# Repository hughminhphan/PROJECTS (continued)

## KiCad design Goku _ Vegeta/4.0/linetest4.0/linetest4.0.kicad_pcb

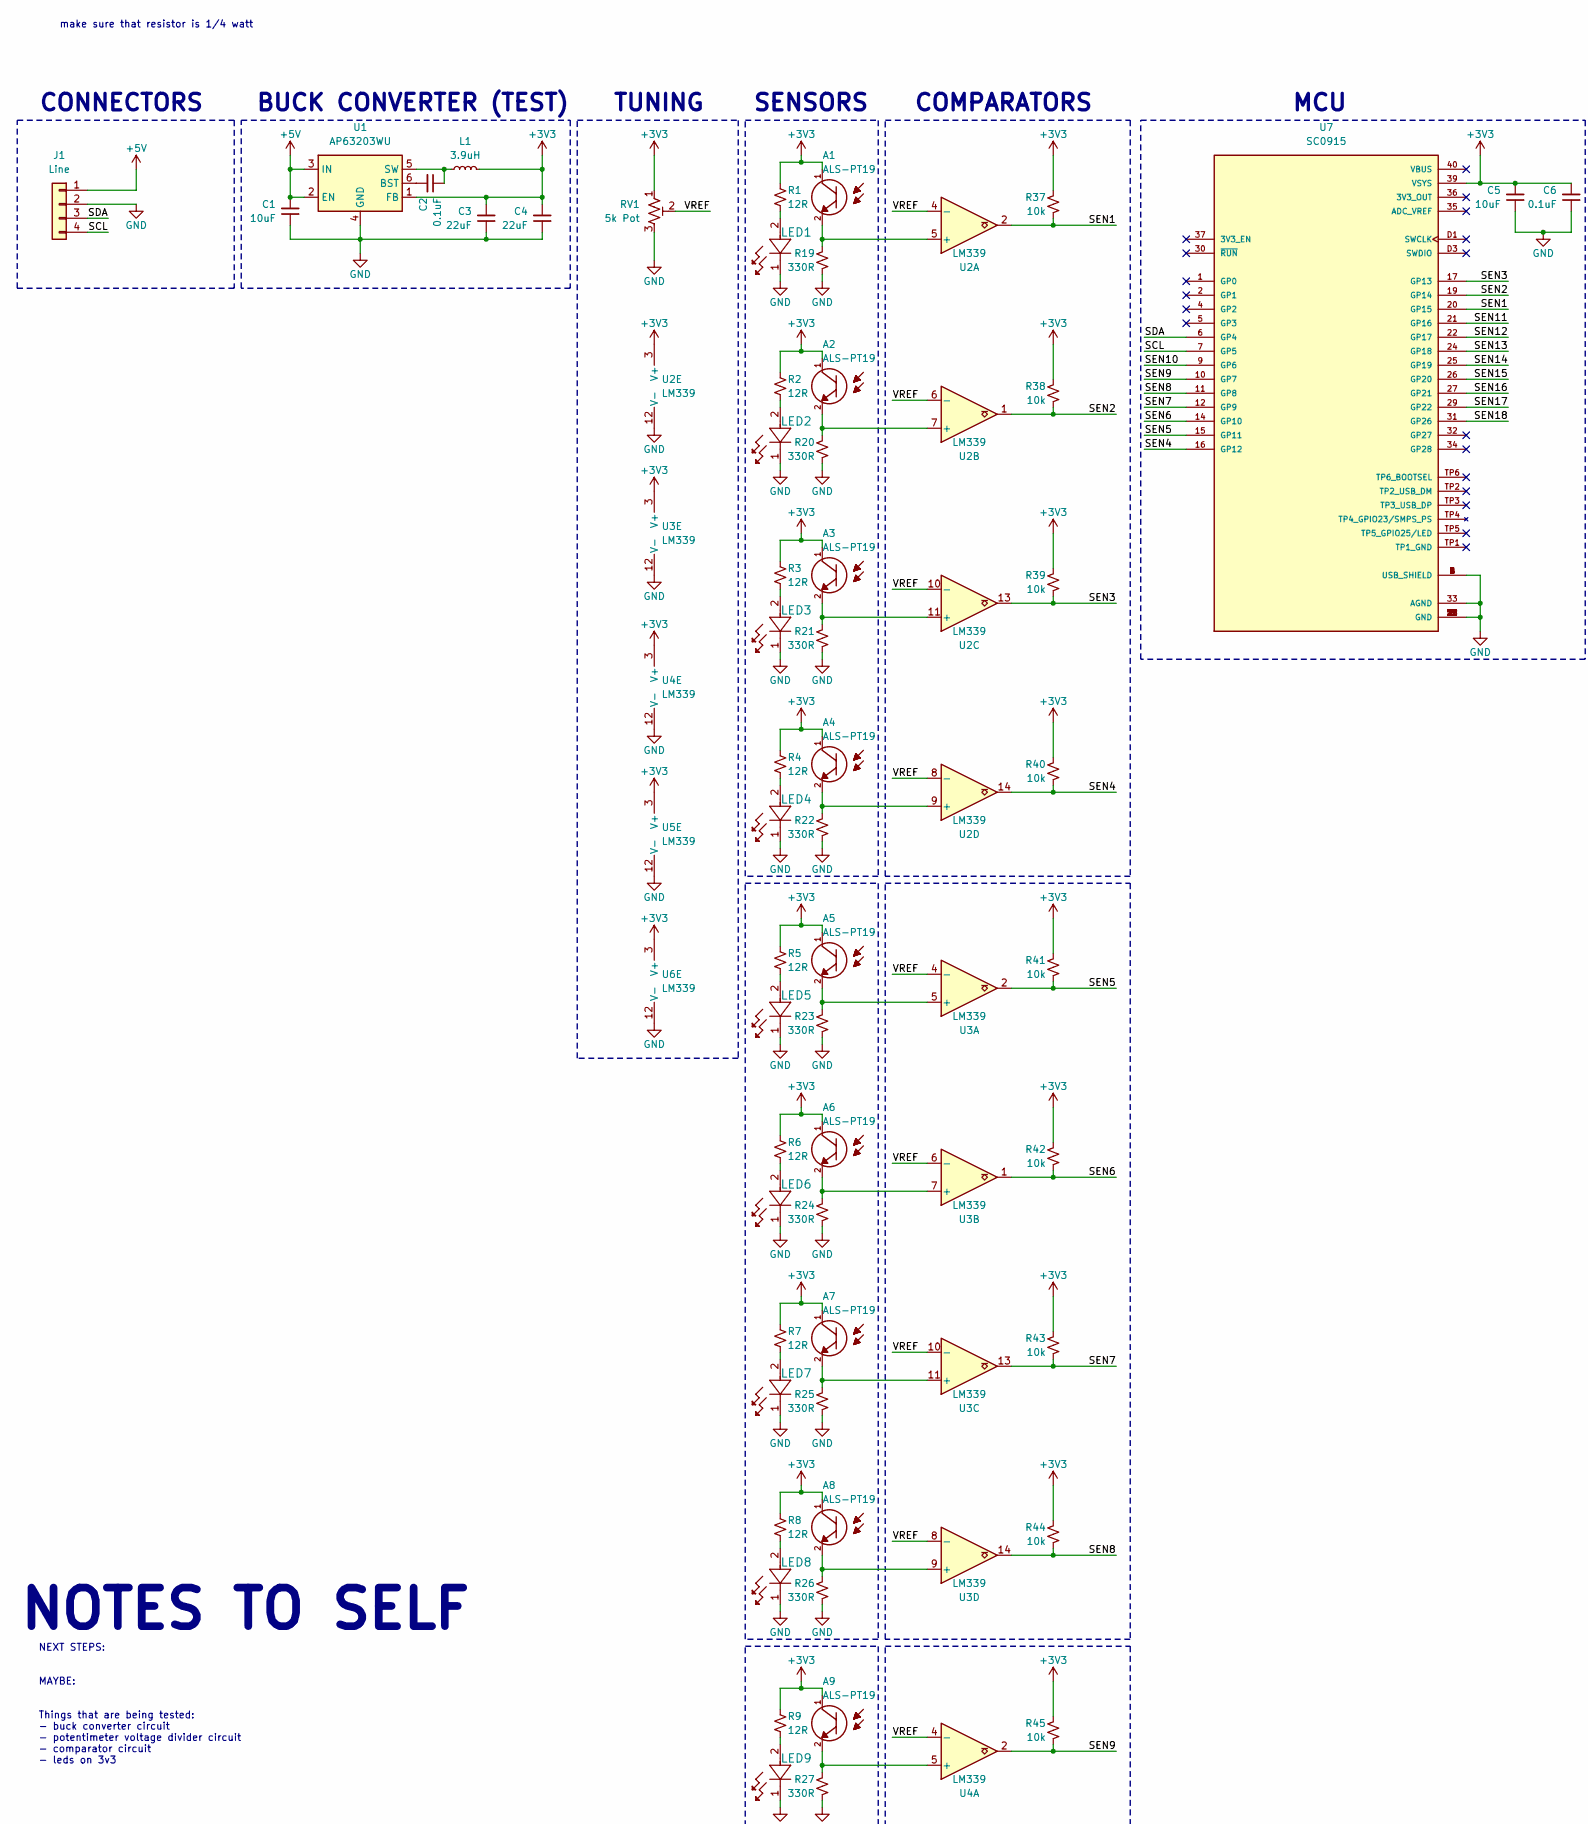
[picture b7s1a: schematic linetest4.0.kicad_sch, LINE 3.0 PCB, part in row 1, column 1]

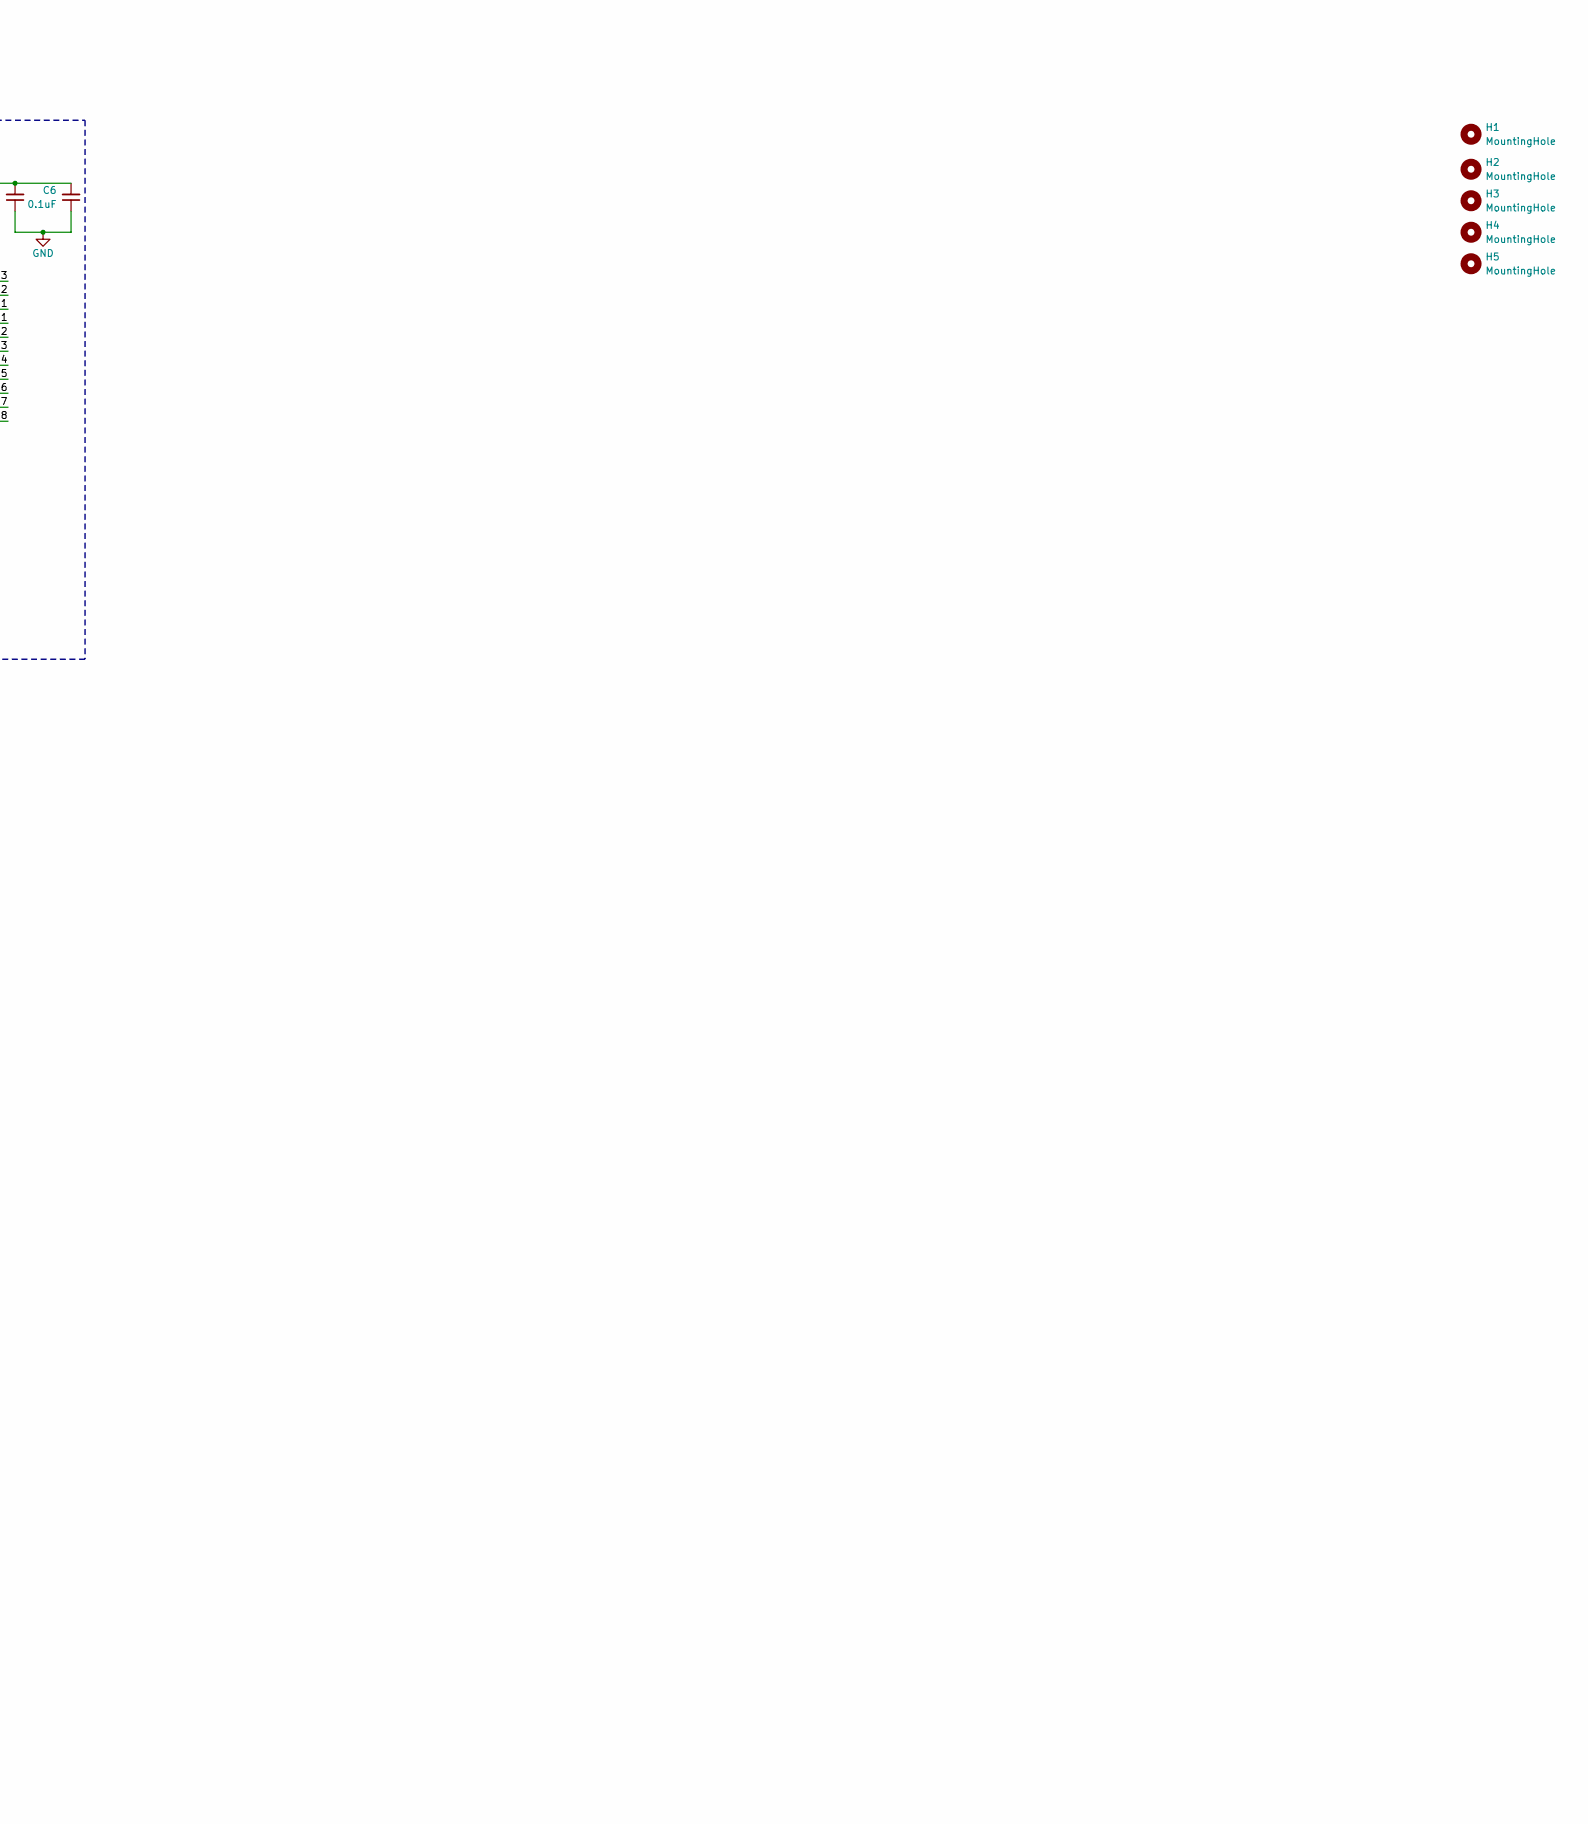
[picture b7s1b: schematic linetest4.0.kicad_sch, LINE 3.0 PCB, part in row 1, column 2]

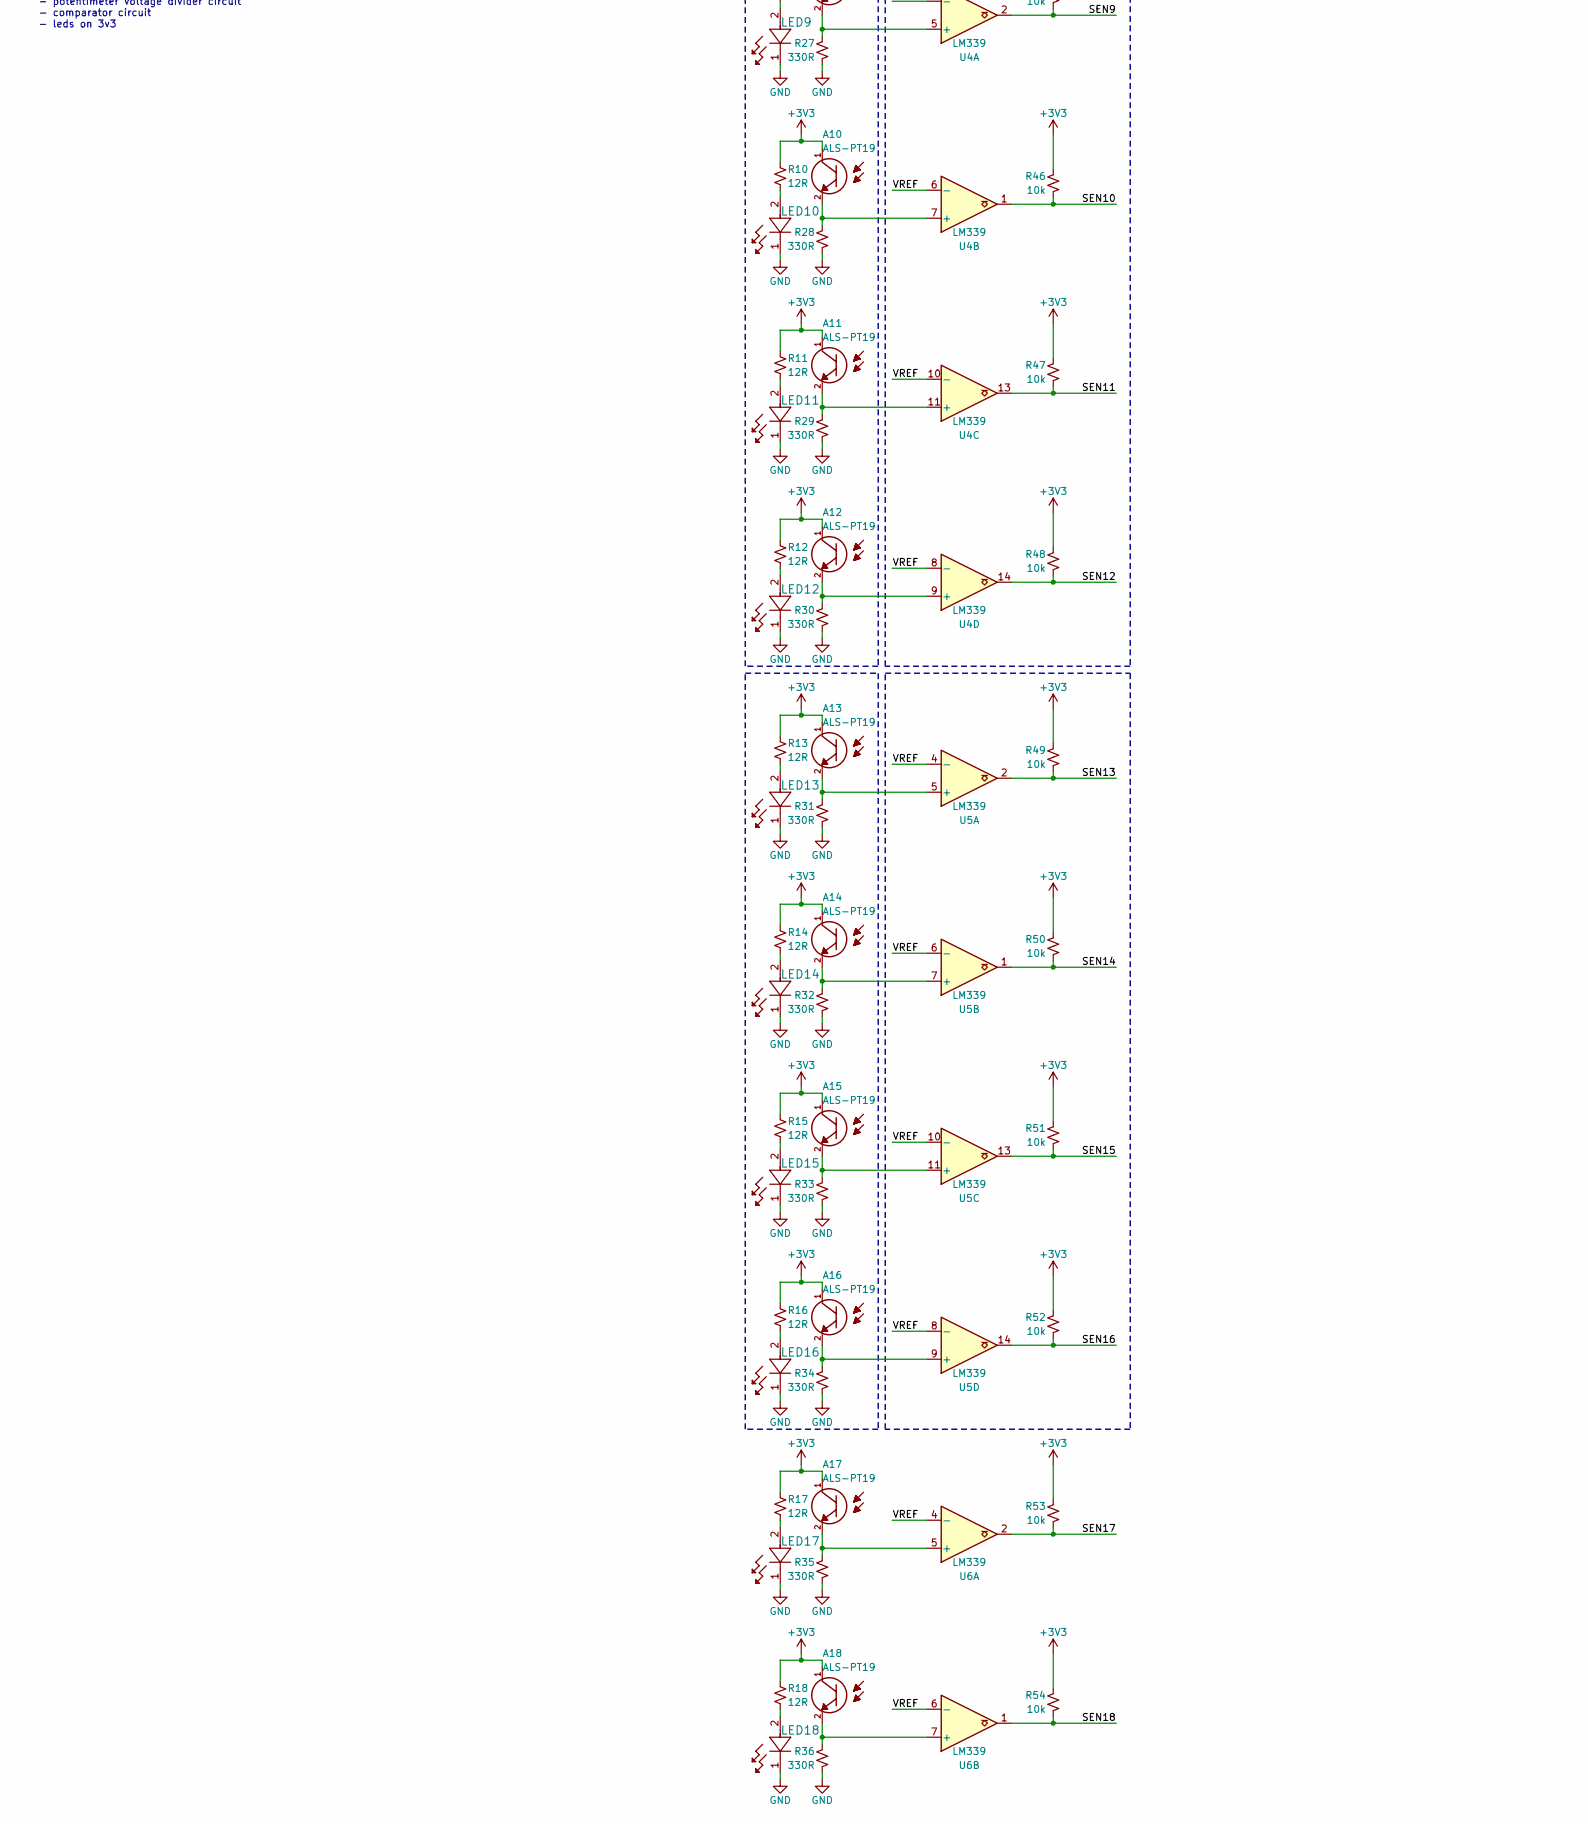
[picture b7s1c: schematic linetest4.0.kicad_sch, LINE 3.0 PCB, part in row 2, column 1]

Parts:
A1, A2, A3, A4, A5, A6, A7, A8, A9, A10, A11, A12, A13, A14, A15, A16, A17, A18: ALS-PT19; XDCR_ALS-PT19-315C_L177_TR8; PARTREV 5
C1, C5: 10uF; 0805
C2, C6: 0.1uF; C_0402_1005Metric
C3, C4: 22uF; 0805
H1, H2, H3, H4, H5: MountingHole; MountingHole_3.2mm_M3
J1: Line; JST_XH_B4B-XH-A_1x04_P2.50mm_Vertical
L1: 3.9uH; L_Bourns-SRU8043
LED1, LED2, LED3, LED4, LED5, LED6, LED7, LED8, LED9, LED10, LED11, LED12, LED13, LED14, LED15, LED16, LED17, LED18: JB2835AWT-W-U30GA0000-N0000001; LED_J2835_CRW
R1, R2, R3, R4, R5, R6, R7, R8, R9, R10, R11, R12, R13, R14, R15, R16, R17, R18: 12R; 0805
R19, R20, R21, R22, R23, R24, R25, R26, R27, R28, R29, R30, R31, R32, R33, R34, R35, R36: 330R; 0805
R37, R38, R39, R40, R41, R42, R43, R44, R45, R46, R47, R48, R49, R50, R51, R52, R53, R54: 10k; 0805
RV1: 5k Pot; Potentiometer_Piher_PT-10-V10_Vertical
U1: AP63203WU; TSOT-23-6
U2, U3, U4, U5, U6: LM339; TSSOP-14_W4.4mm
U7: SC0915; MODULE_SC0915; PARTREV 1.9

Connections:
+3V3: A1.1, A2.1, A3.1, A4.1, A5.1, A6.1, A7.1, A8.1, A9.1, A10.1, A11.1, A12.1, A13.1, A14.1, A15.1, A16.1, A17.1, A18.1, C3.2, C4.2, C5.2, C6.2, L1.2, R1.1, R2.1, R3.1, R4.1, R5.1, R6.1, R7.1, R8.1, R9.1, R10.1, R11.1, R12.1, R13.1, R14.1, R15.1, R16.1, R17.1, R18.1, R37.2, R38.2, R39.2, R40.2, R41.2, R42.2, R43.2, R44.2, R45.2, R46.2, R47.2, R48.2, R49.2, R50.2, R51.2, R52.2, R53.2, R54.2, RV1.1, U1.1 (FB), U2.3 (V+), U3.3 (V+), U4.3 (V+), U5.3 (V+), U6.3 (V+), U7.39 (VSYS)
+5V: C1.2, J1.1, U1.2 (EN), U1.3 (IN)
/SCL: J1.4, U7.7 (GP5)
/SDA: J1.3, U7.6 (GP4)
/SEN1: R37.1, U2.2, U7.20 (GP15)
/SEN2: R38.1, U2.1, U7.19 (GP14)
/SEN3: R39.1, U2.13, U7.17 (GP13)
/SEN4: R40.1, U2.14, U7.16 (GP12)
/SEN5: R41.1, U3.2, U7.15 (GP11)
/SEN6: R42.1, U3.1, U7.14 (GP10)
/SEN7: R43.1, U3.13, U7.12 (GP9)
/SEN8: R44.1, U3.14, U7.11 (GP8)
/SEN9: R45.1, U4.2, U7.10 (GP7)
/SEN10: R46.1, U4.1, U7.9 (GP6)
/SEN11: R47.1, U4.13, U7.21 (GP16)
/SEN12: R48.1, U4.14, U7.22 (GP17)
/SEN13: R49.1, U5.2, U7.24 (GP18)
/SEN14: R50.1, U5.1, U7.25 (GP19)
/SEN15: R51.1, U5.13, U7.26 (GP20)
/SEN16: R52.1, U5.14, U7.27 (GP21)
/SEN17: R53.1, U6.2, U7.29 (GP22)
/SEN18: R54.1, U6.1, U7.31 (GP26)
/VREF: RV1.2, U2.4 (-), U2.6 (-), U2.8 (-), U2.10 (-), U3.4 (-), U3.6 (-), U3.8 (-), U3.10 (-), U4.4 (-), U4.6 (-), U4.8 (-), U4.10 (-), U5.4 (-), U5.6 (-), U5.8 (-), U5.10 (-), U6.4 (-), U6.6 (-)
GND: C1.1, C3.1, C4.1, C5.1, C6.1, J1.2, LED1.1, LED2.1, LED3.1, LED4.1, LED5.1, LED6.1, LED7.1, LED8.1, LED9.1, LED10.1, LED11.1, LED12.1, LED13.1, LED14.1, LED15.1, LED16.1, LED17.1, LED18.1, R19.1, R20.1, R21.1, R22.1, R23.1, R24.1, R25.1, R26.1, R27.1, R28.1, R29.1, R30.1, R31.1, R32.1, R33.1, R34.1, R35.1, R36.1, RV1.3, U1.4 (GND), U2.12 (V-), U3.12 (V-), U4.12 (V-), U5.12 (V-), U6.12 (V-), U7.3 (GND), U7.8 (GND), U7.13 (GND), U7.18 (GND), U7.23 (GND), U7.28 (GND), U7.33 (AGND), U7.38 (GND), U7.A (USB_SHIELD), U7.B (USB_SHIELD), U7.C (USB_SHIELD), U7.D (USB_SHIELD), U7.D2 (GND)
unnamed: LED1.2, R1.2
unnamed: LED2.2, R2.2
unnamed: LED3.2, R3.2
unnamed: LED4.2, R4.2
unnamed: LED5.2, R5.2
unnamed: LED6.2, R6.2
unnamed: LED7.2, R7.2
unnamed: LED8.2, R8.2
unnamed: LED9.2, R9.2
unnamed: LED10.2, R10.2
unnamed: LED11.2, R11.2
unnamed: LED12.2, R12.2
unnamed: LED13.2, R13.2
unnamed: LED14.2, R14.2
unnamed: LED15.2, R15.2
unnamed: LED16.2, R16.2
unnamed: LED17.2, R17.2
unnamed: LED18.2, R18.2
unnamed: C2.2, U1.6 (BST)
unnamed: C2.1, L1.1, U1.5 (SW)
unnamed: A1.2, R19.2, U2.5 (+)
unnamed: A2.2, R20.2, U2.7 (+)
unnamed: A3.2, R21.2, U2.11 (+)
unnamed: A4.2, R22.2, U2.9 (+)
unnamed: A5.2, R23.2, U3.5 (+)
unnamed: A6.2, R24.2, U3.7 (+)
unnamed: A7.2, R25.2, U3.11 (+)
unnamed: A8.2, R26.2, U3.9 (+)
unnamed: A9.2, R27.2, U4.5 (+)
unnamed: A10.2, R28.2, U4.7 (+)
unnamed: A11.2, R29.2, U4.11 (+)
unnamed: A12.2, R30.2, U4.9 (+)
unnamed: A13.2, R31.2, U5.5 (+)
unnamed: A14.2, R32.2, U5.7 (+)
unnamed: A15.2, R33.2, U5.11 (+)
unnamed: A16.2, R34.2, U5.9 (+)
unnamed: A17.2, R35.2, U6.5 (+)
unnamed: A18.2, R36.2, U6.7 (+)

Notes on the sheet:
NOTES TO SELF
NEXT STEPS: MAYBE: Things that are being tested: - buck converter circuit - potentimeter voltage divider circuit - comparator circuit - leds on 3v3
SENSORS
TUNING
make sure that resistor is 1/4 watt
CONNECTORS
MCU
BUCK CONVERTER (TEST)
COMPARATORS

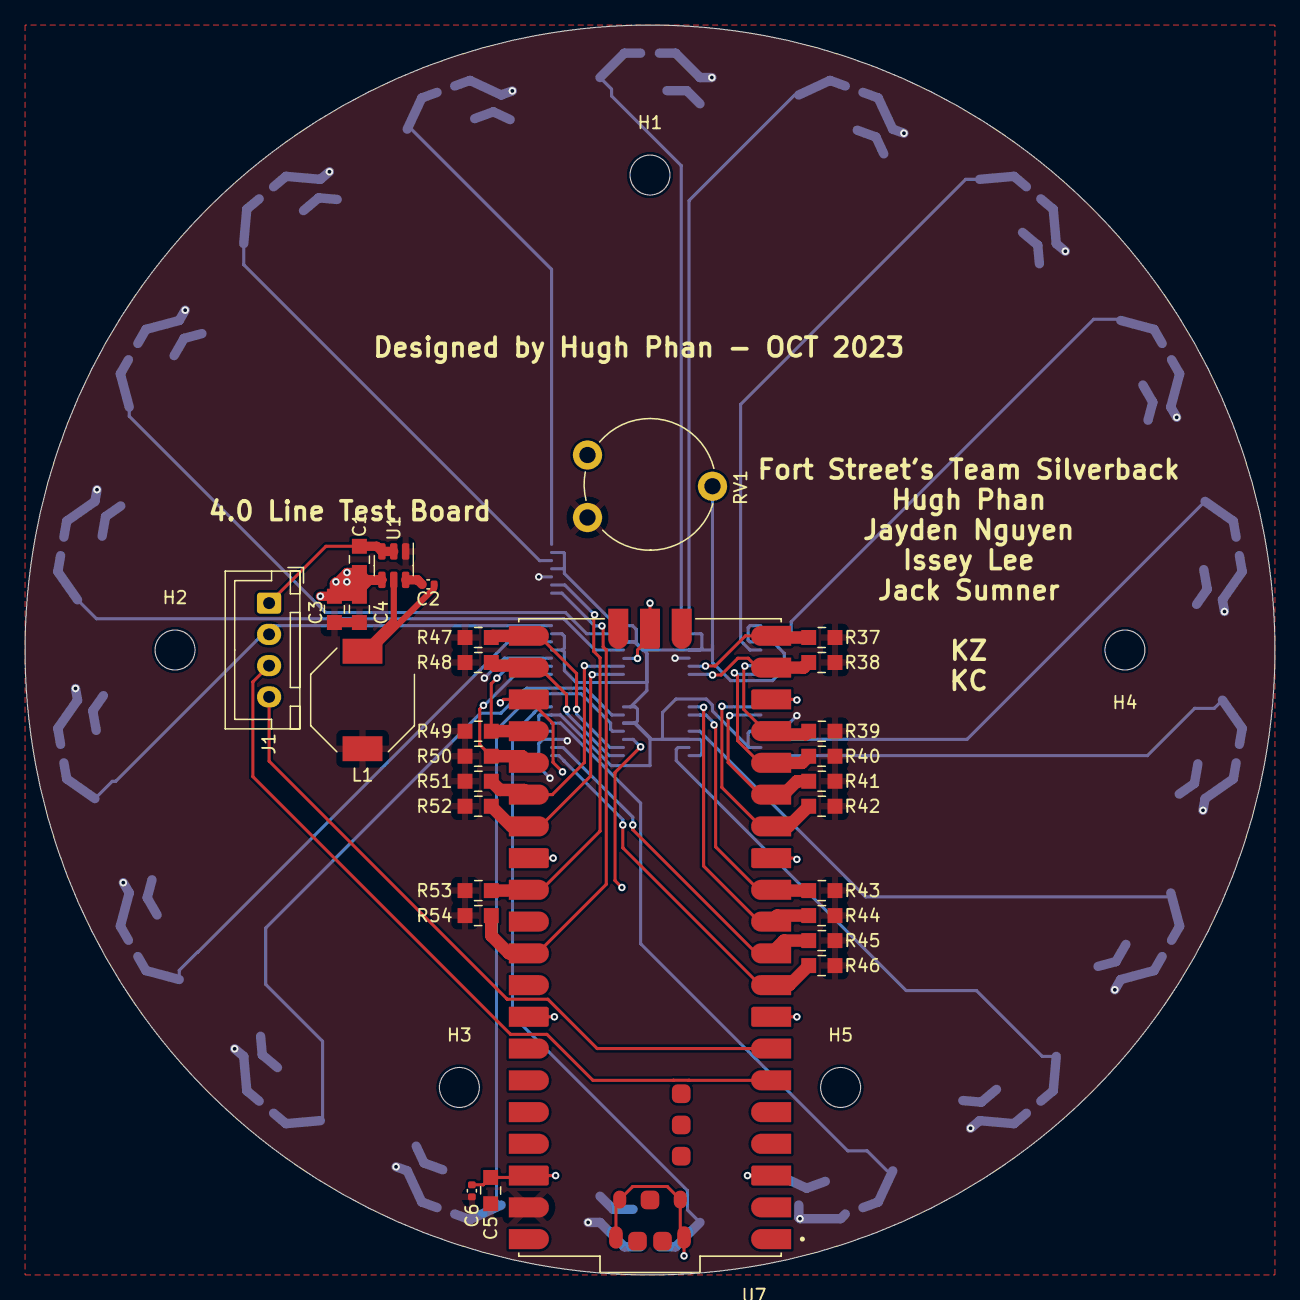
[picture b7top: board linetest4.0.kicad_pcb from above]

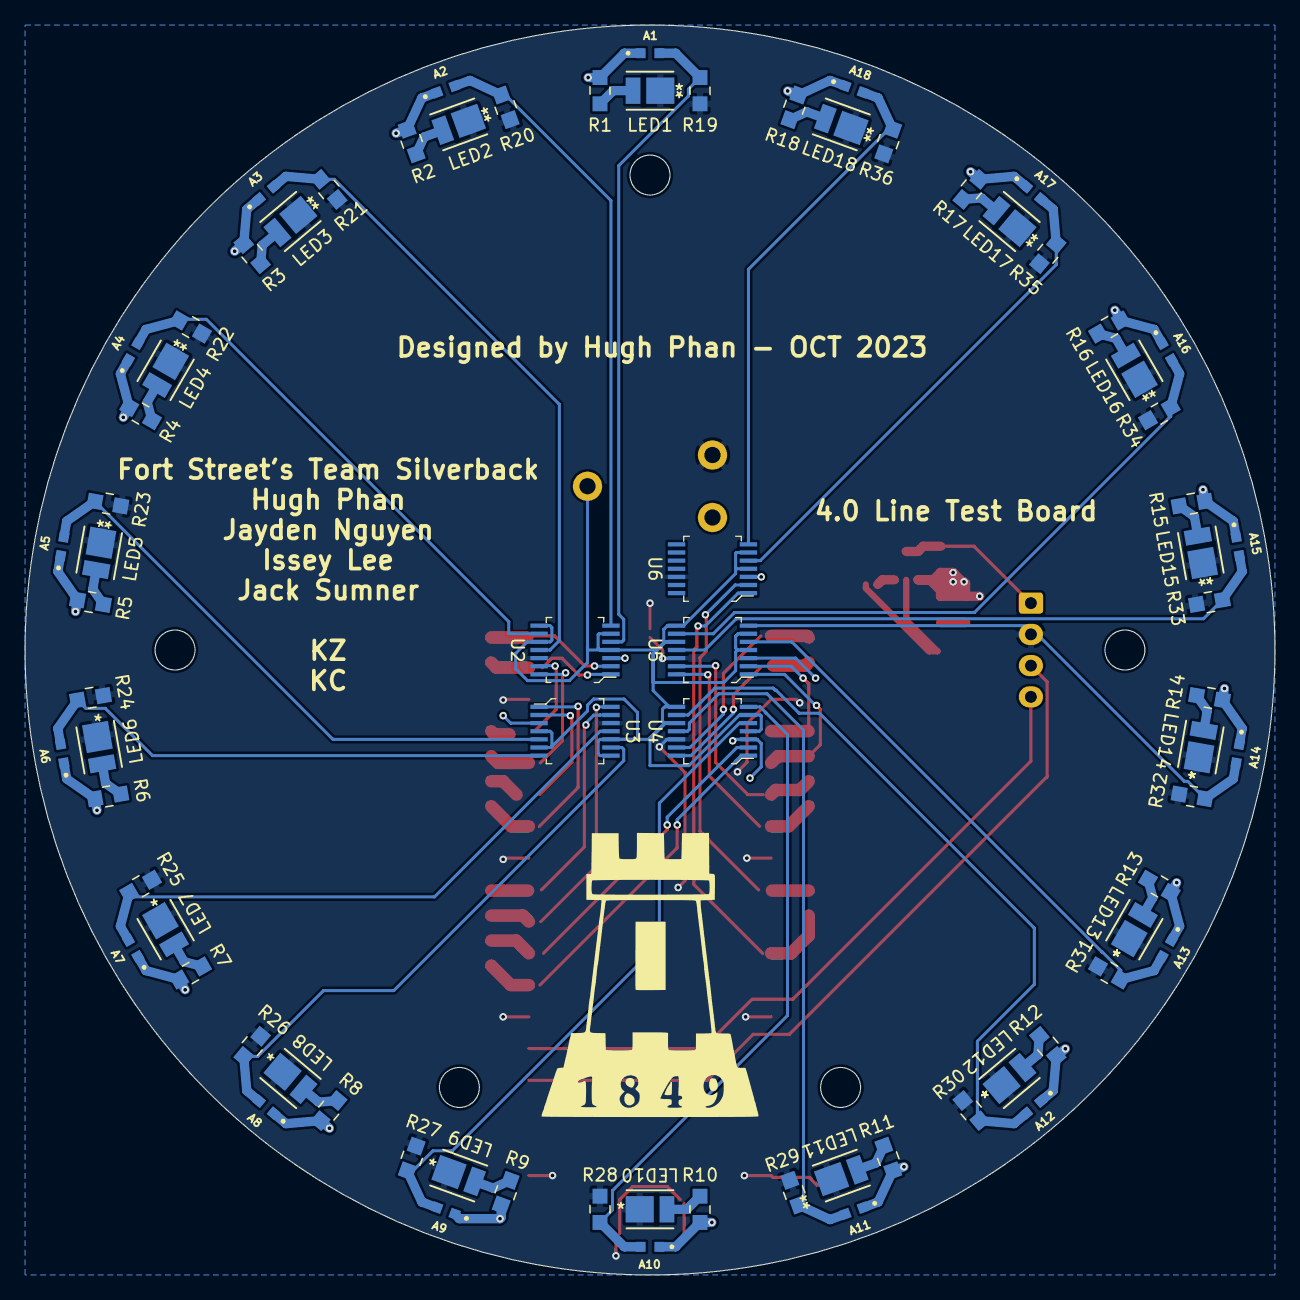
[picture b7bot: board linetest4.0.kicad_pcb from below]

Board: 2 copper layers, 100.0 x 100.0 mm, 111 parts (77 on the bottom side), 62 nets.

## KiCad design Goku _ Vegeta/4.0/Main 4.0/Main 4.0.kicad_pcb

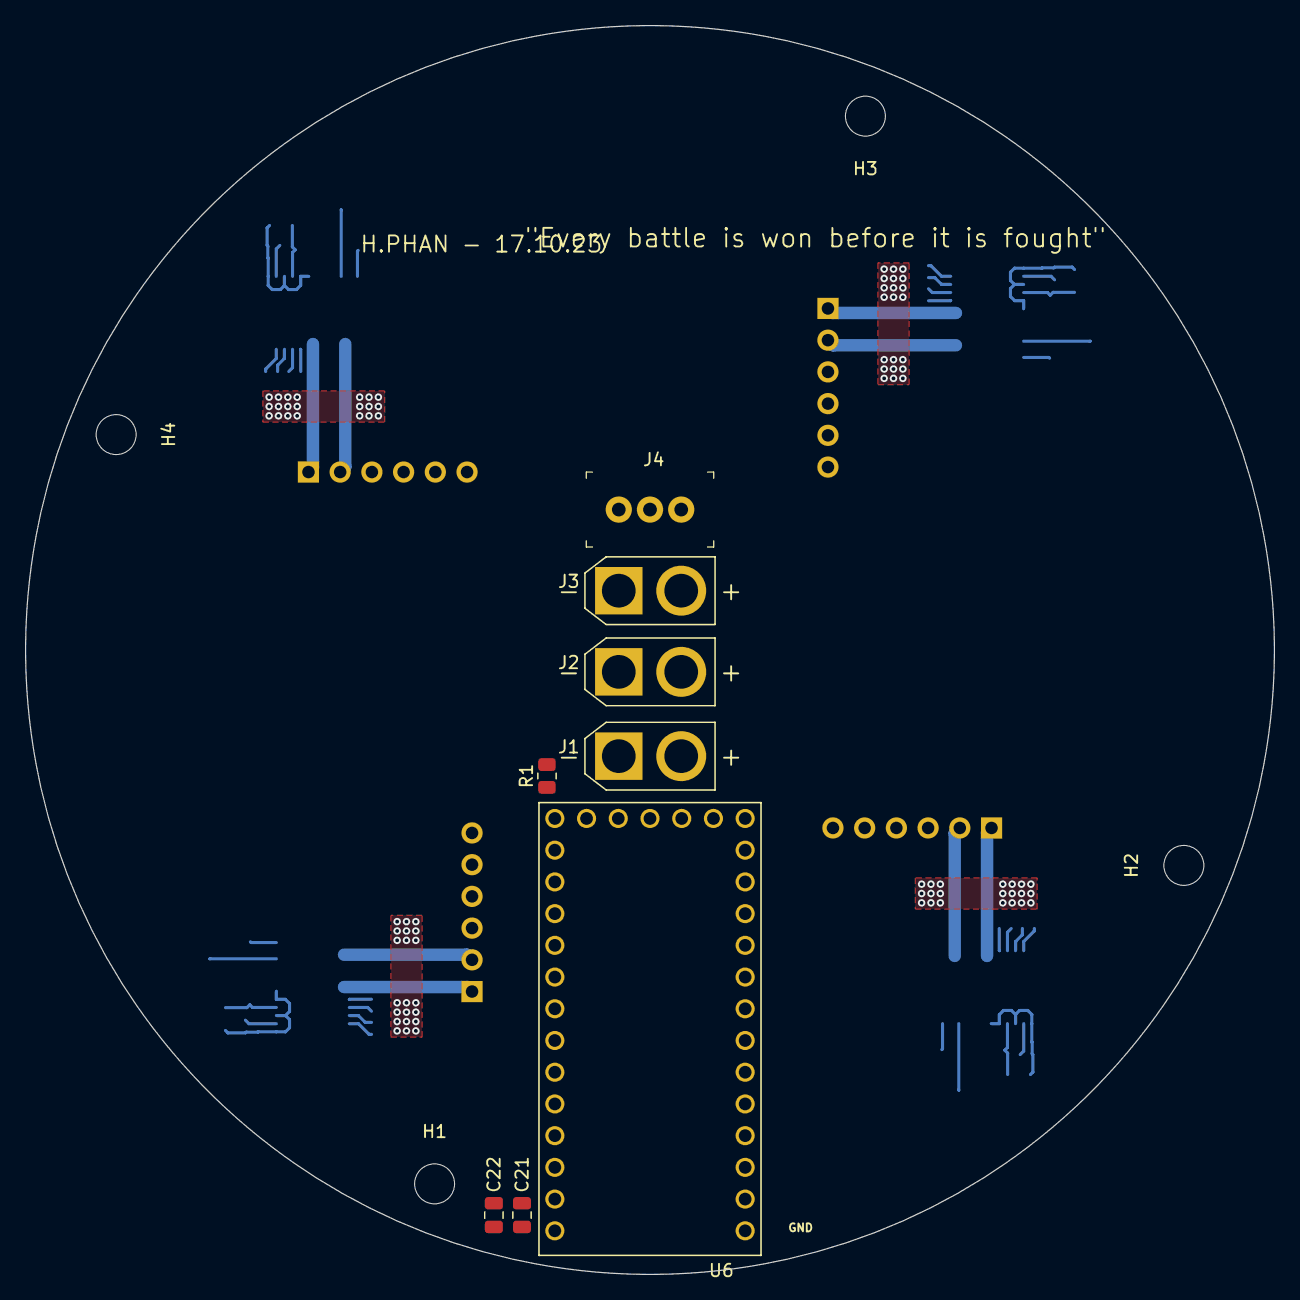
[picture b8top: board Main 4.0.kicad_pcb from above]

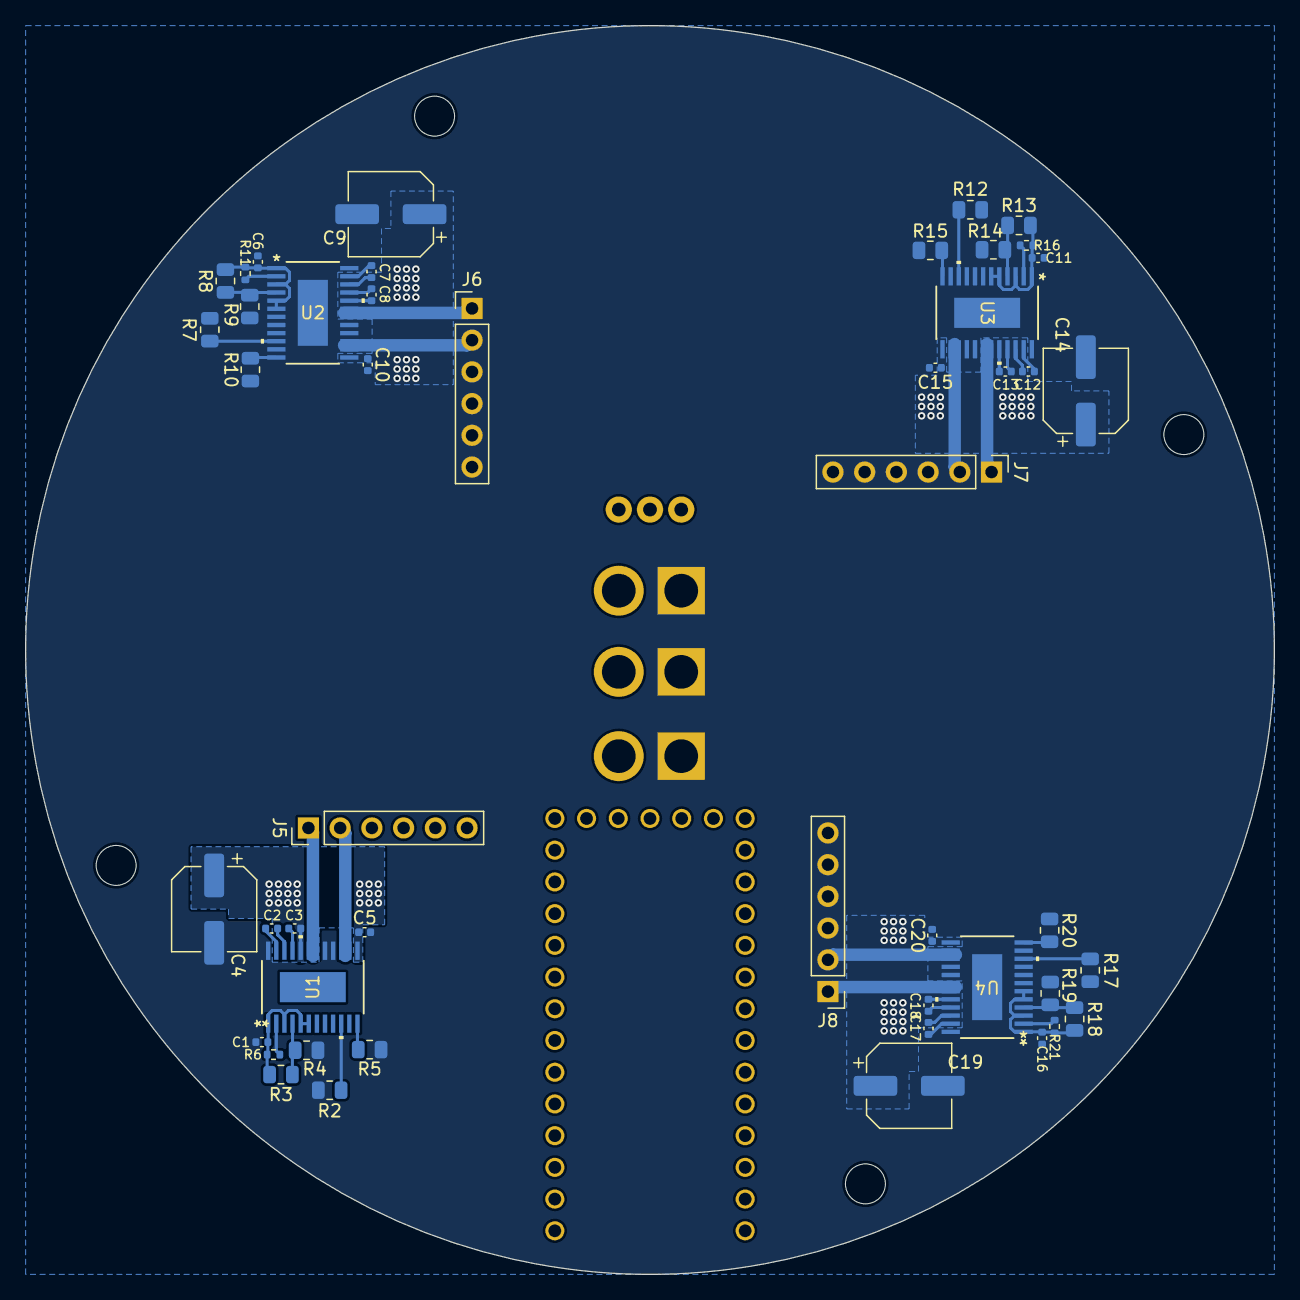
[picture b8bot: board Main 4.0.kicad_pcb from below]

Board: 2 copper layers, 100.0 x 100.0 mm, 60 parts (48 on the bottom side), 64 nets.

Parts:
C1, C3, C6, C8, C11, C13, C16, C18: 1uF; C_0402_1005Metric
C2, C7, C12, C17: 47nF; C_0402_1005Metric
C4, C9, C14, C19: 100uF; CP_Elec_6.3x7.7
C5, C10, C15, C20: 0.1uF; C_0402_1005Metric
C21: 10uF; C_0805_2012Metric
C22: 100nF; C_0805_2012Metric
H1, H2, H3, H4: MountingHole; MountingHole_3.2mm_M3
J1: BATT; AMASS_XT30U-F_1x02_P5.0mm_Vertical
J2: 5V Buck; AMASS_XT30U-F_1x02_P5.0mm_Vertical
J3: 3V3 Buck; AMASS_XT30U-F_1x02_P5.0mm_Vertical
J4: I2C; PinHeader_1x3_P2.5mm_Drill1.1mm
J5, J6, J7, J8: M1; PinHeader_1x06_P2.54mm_Vertical
R1, R3, R8, R13, R18: 0R; R_0805_2012Metric
R2, R5, R7, R10, R12, R15, R17, R20: 363R; R_0805_2012Metric
R4, R9, R14, R19: 3M; R_0805_2012Metric
R6, R11, R16, R21: 10k; R_0402_1005Metric
U1, U2, U3, U4: DRV8873HPWPR; PWP24_TEX
U6: DEV-15583; MODULE_DEV-15583

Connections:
+3V3: J3.2, J5.4, J6.4, J7.4, J8.4
+5V: C21.1, C22.1, J2.2, U1.11 (NSLEEP), U2.11 (NSLEEP), U3.11 (NSLEEP), U4.11 (NSLEEP), U6.VIN
+15V: C3.2, C4.1, C5.1, C8.2, C9.1, C10.1, C13.2, C14.1, C15.1, C18.2, C19.1, C20.1, J1.2, U1.13 (VM), U1.20 (VM), U2.13 (VM), U2.20 (VM), U3.13 (VM), U3.20 (VM), U4.13 (VM), U4.20 (VM)
/DISABLE: U1.9 (DISABLE), U2.9 (DISABLE), U3.9 (DISABLE), U4.9 (DISABLE), U6.12
/ENC1A: J5.5, U6.10
/ENC1B: J5.6, U6.11
/ENC2A: J6.5, U6.15
/ENC2B: J6.6, U6.14
/ENC3A: J7.5, U6.23
/ENC3B: J7.6, U6.22
/ENC4A: J8.5, U6.21
/ENC4B: J8.6, U6.20
/M1A: J5.1, U1.18 (OUT1), U1.19 (OUT1)
/M1B: J5.2, U1.14 (OUT2), U1.15 (OUT2)
/M1IN1: U1.7 (EN/IN1), U6.2
/M1IN2: U1.8 (PH/IN2), U6.3
/M2A: J6.1, U2.18 (OUT1), U2.19 (OUT1)
/M2B: J6.2, U2.14 (OUT2), U2.15 (OUT2)
/M2IN1: U2.7 (EN/IN1), U6.4
/M2IN2: U2.8 (PH/IN2), U6.5
/M3A: J7.1, U3.18 (OUT1), U3.19 (OUT1)
/M3B: J7.2, U3.14 (OUT2), U3.15 (OUT2)
/M3IN1: U3.7 (EN/IN1), U6.6
/M3IN2: U3.8 (PH/IN2), U6.7
/M4A: J8.1, U4.18 (OUT1), U4.19 (OUT1)
/M4B: J8.2, U4.14 (OUT2), U4.15 (OUT2)
/M4IN1: U4.7 (EN/IN1), U6.8
/M4IN2: U4.8 (PH/IN2), U6.9
/SCL: J4.1, U6.19
/SDA: J4.2, U6.18
GNDPWR: C1.2, C4.2, C5.2, C6.2, C9.2, C10.2, C11.2, C14.2, C15.2, C16.2, C19.2, C20.2, J1.1, J2.1, J3.1, R1.2, R2.2, R4.2, R5.2, R7.2, R9.2, R10.2, R12.2, R14.2, R15.2, R17.2, R19.2, R20.2, U1.16 (SRC), U1.17 (SRC), U1.24 (GND), U2.16 (SRC), U2.17 (SRC), U2.24 (GND), U3.16 (SRC), U3.17 (SRC), U3.24 (GND), U4.16 (SRC), U4.17 (SRC), U4.24 (GND)
GNDS: C21.2, C22.2, J4.3, J5.3, J6.3, J7.3, J8.3, R1.1, U6.G1, U6.G2, U6.G3
unnamed: C2.2, U1.22 (CPH)
unnamed: C2.1, U1.23 (CPL)
unnamed: C1.1, R3.1, R6.1, U1.1 (DVDD), U1.3 (MODE), U1.5 (NITRIP), U1.6 (NOL)
unnamed: R2.1, U1.10 (IPROPI1)
unnamed: R5.1, U1.12 (IPROPI2)
unnamed: R6.2, U1.2 (NFAULT)
unnamed: R3.2, R4.1, U1.4 (SR)
unnamed: C3.1, U1.21 (VCP)
unnamed: C7.2, U2.22 (CPH)
unnamed: C7.1, U2.23 (CPL)
unnamed: C6.1, R8.1, R11.1, U2.1 (DVDD), U2.3 (MODE), U2.5 (NITRIP), U2.6 (NOL)
unnamed: R7.1, U2.10 (IPROPI1)
unnamed: R10.1, U2.12 (IPROPI2)
unnamed: R11.2, U2.2 (NFAULT)
unnamed: R8.2, R9.1, U2.4 (SR)
unnamed: C8.1, U2.21 (VCP)
unnamed: C12.2, U3.22 (CPH)
unnamed: C12.1, U3.23 (CPL)
unnamed: C11.1, R13.1, R16.1, U3.1 (DVDD), U3.3 (MODE), U3.5 (NITRIP), U3.6 (NOL)
unnamed: R12.1, U3.10 (IPROPI1)
unnamed: R15.1, U3.12 (IPROPI2)
unnamed: R16.2, U3.2 (NFAULT)
unnamed: R13.2, R14.1, U3.4 (SR)
unnamed: C13.1, U3.21 (VCP)
unnamed: C17.2, U4.22 (CPH)
unnamed: C17.1, U4.23 (CPL)
unnamed: C16.1, R18.1, R21.1, U4.1 (DVDD), U4.3 (MODE), U4.5 (NITRIP), U4.6 (NOL)
unnamed: R17.1, U4.10 (IPROPI1)
unnamed: R20.1, U4.12 (IPROPI2)
unnamed: R21.2, U4.2 (NFAULT)
unnamed: R18.2, R19.1, U4.4 (SR)
unnamed: C18.1, U4.21 (VCP)

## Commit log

2023-08-14 Intro Epic Commit Test
    testing
2023-08-15 new visor pcb - didnt change anything just checking
2023-08-18 Line 3.0 schematic
2023-08-18 Line 3.0 SCH 1st draft done + started working on SCH for main 3.0
2023-08-18 created sumonyx v2.1
    difference between v2 and v2.1 is that v2.1 is done properly and is made to be cleaner and shipped out
2023-08-19 added notes to sumonyx pcbs
2023-08-22 sumonyx code
    need to get
2023-08-24 sumonyx pcb change to visor ic
2023-08-24 save docs
2023-09-01 Started 3.1 PCBs
2023-09-02 abt halfway done with line 3.0
2023-09-03 Line 3.0 save
2023-09-03 CLEAN UP 3.0 LINE SCH
2023-09-03 line 3.0 - good for the night
2023-09-04 LINE 3.0 - teensy - M driver routing + added teensy programming. + on off switch breakout
2023-09-05 LINE PCB 3.0 BASICALLY DONE!! NOW JUST GOTTA ADD SILKSCREEN!
2023-09-05 LINE 3.0 Update
    -Updated to have caps on power rails
    -imrpoves tolerance of 100uf capacitor
    -main power cable went from xt60 to xt30
    - remove outer wheel guard
2023-09-09 move to 3.1
2023-09-14 MAIN 3.1 DONE no silkscreen
2023-09-15 Main and Line 3.1 done w/ silkscreen
2023-09-16 main 3.1 edit actualy done now i think...
2023-09-16 sch for sumonyx 2.1 pcb
2023-09-16 commit b4 sleep
2023-09-17 main 3.1 fixup
2023-09-17 new mfr for pcbs
2023-12-15 kjwefqkwenfqerlgk
2024-09-15 name change for windows compatibility
    totlololoo
2024-09-15 sbrcotnrollerm update from windows laptop
    dcefefefefe
2024-09-15 what is happening
2024-09-15 ready for mfr
2024-09-15 sbr2code
2024-09-15 demo
2024-09-17 updated code
2024-09-19 pcb mfr
2024-09-20 troll
2024-10-08 sbr lol and the like
2025-01-09 testing the sync
2025-01-09 rgrgrg
